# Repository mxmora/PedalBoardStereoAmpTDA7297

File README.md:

# PedalBoardStereoAmpTDA7297
PedalBoardStereoAmpTDA7297

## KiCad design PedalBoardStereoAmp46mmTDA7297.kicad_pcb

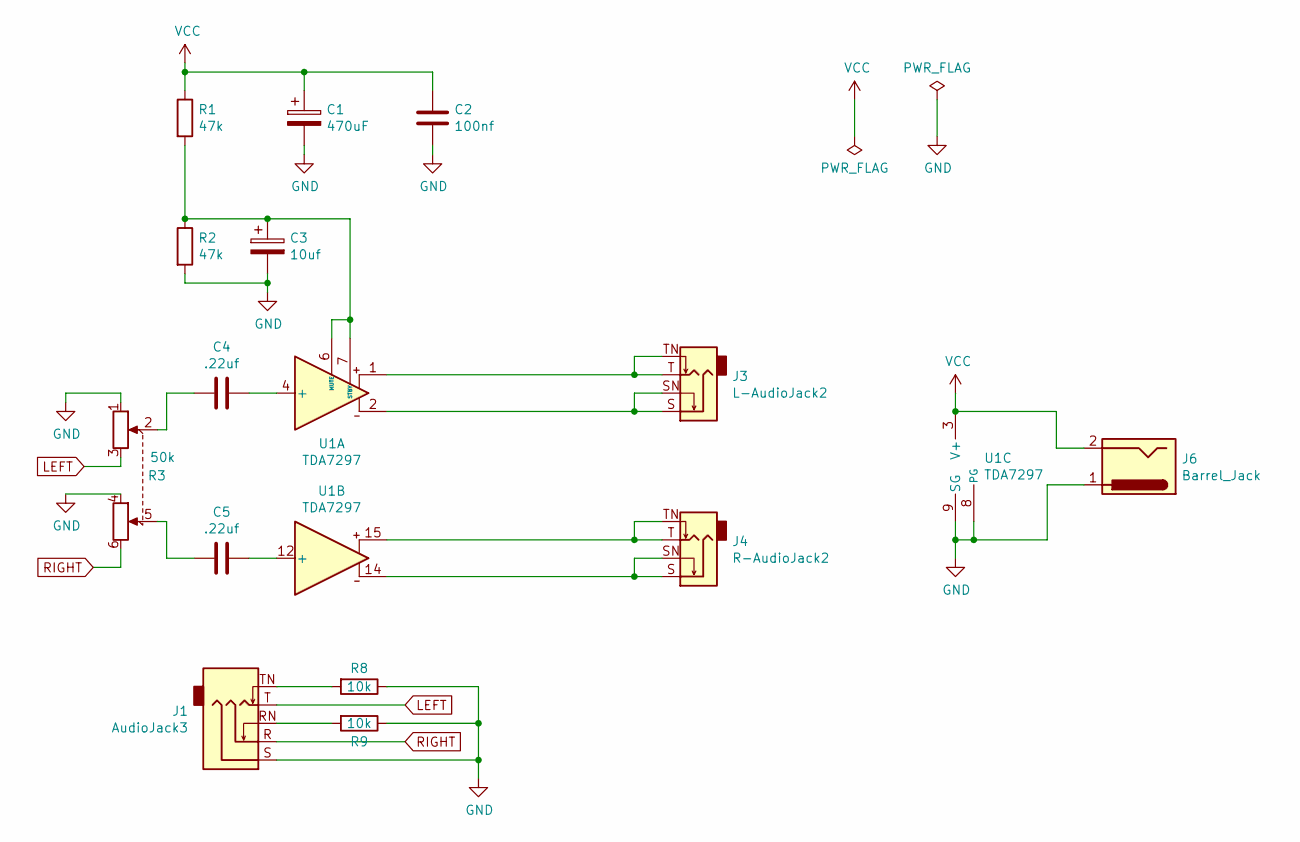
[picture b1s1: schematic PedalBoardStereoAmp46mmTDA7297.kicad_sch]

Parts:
C1: 470uF; CP_Radial_D12.5mm_P5.00mm
C2: 100nf; C_Rect_L7.2mm_W2.5mm_P5.00mm_FKS2_FKP2_MKS2_MKP2
C3: 10uf; CP_Radial_D5.0mm_P2.50mm
C4, C5: .22uf; C_Rect_L7.2mm_W3.0mm_P5.00mm_FKS2_FKP2_MKS2_MKP2
J1: AudioJack3; Jack_3.5mm_CUI_SJ1-3535NG_Horizontal_CircularHoles
J3: L-AudioJack2; Jack_6.35mm_Neutrik_NMJ4HFD2_Horizontal
J4: R-AudioJack2; Jack_6.35mm_Neutrik_NMJ4HFD2_Horizontal
J6: Barrel_Jack; TerminalBlock_bornier-2_P5.08mm
R1, R2: 47k; R_Axial_DIN0207_L6.3mm_D2.5mm_P5.08mm_Vertical
R3: 50k; Potentiometer_Alps_RK09L_Double_Horizontal
R8, R9: 10k; R_Axial_DIN0207_L6.3mm_D2.5mm_P5.08mm_Vertical
U1: TDA7297; TO-220-15_P2.54x2.54mm_StaggerOdd_Lead4.58mm_Vertical

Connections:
GND: C1.2, C2.2, C3.2, J1.S, J6.1, R2.2, R3.1, R3.4, R8.1, R9.1, U1.8 (PG), U1.9 (SG)
LEFT: J1.T, R3.3
unnamed: C3.1, R1.2, R2.1, U1.6 (MUTE), U1.7 (STBY)
unnamed: C4.1, U1.4 (+)
unnamed: C4.2, R3.2
unnamed: C5.1, U1.12 (+)
unnamed: C5.2, R3.5
unnamed: J1.RN, R9.2
unnamed: J1.TN, R8.2
unnamed: J3.S, J3.SN, U1.2
unnamed: J3.T, J3.TN, U1.1
unnamed: J4.S, J4.SN, U1.14
unnamed: J4.T, J4.TN, U1.15
RIGHT: J1.R, R3.6
VCC: C1.1, C2.1, J6.2, R1.1, U1.3 (V+), U1.13 (V+)

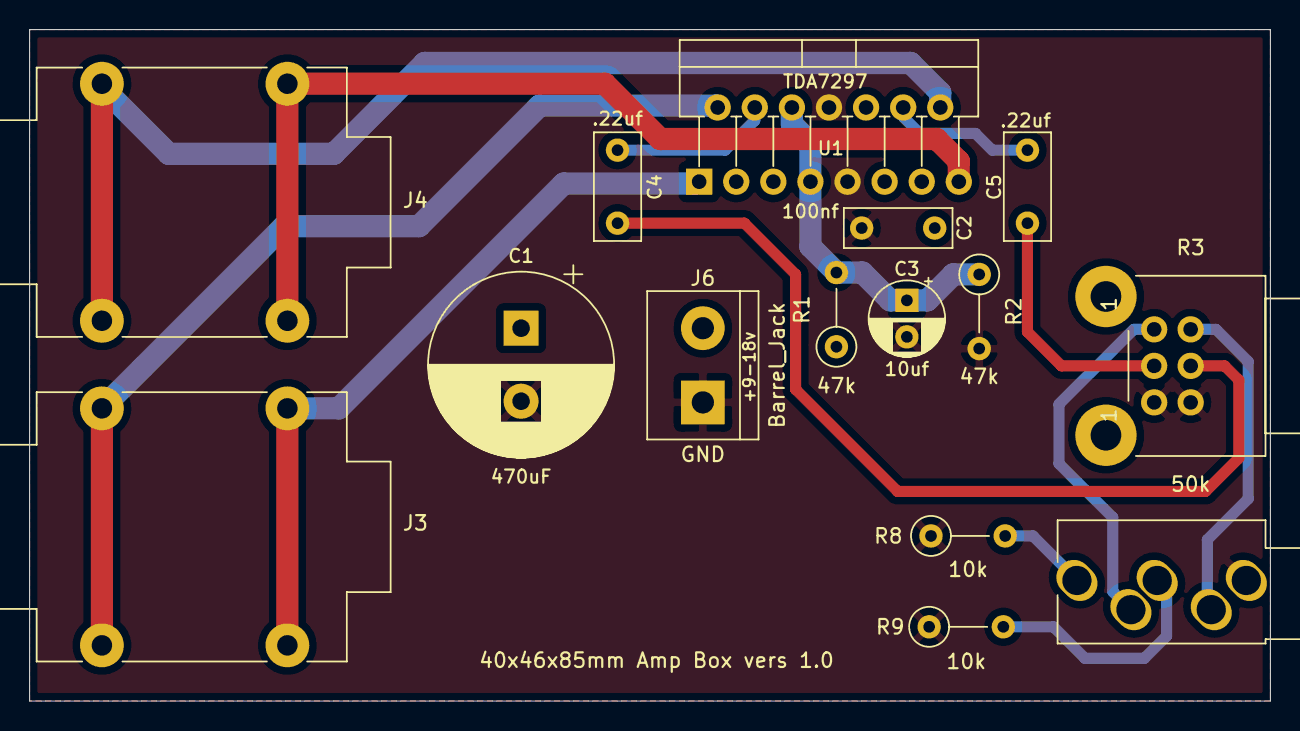
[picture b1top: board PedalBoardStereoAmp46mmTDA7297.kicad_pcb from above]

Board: 2 copper layers, 85.0 x 46.0 mm, 15 parts (0 on the bottom side), 15 nets.

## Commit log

2020-11-20 first checkin
2020-11-21 update with pots connector
2020-11-21 fix up schematic
2021-01-05 update design
2021-12-25 update to v6
